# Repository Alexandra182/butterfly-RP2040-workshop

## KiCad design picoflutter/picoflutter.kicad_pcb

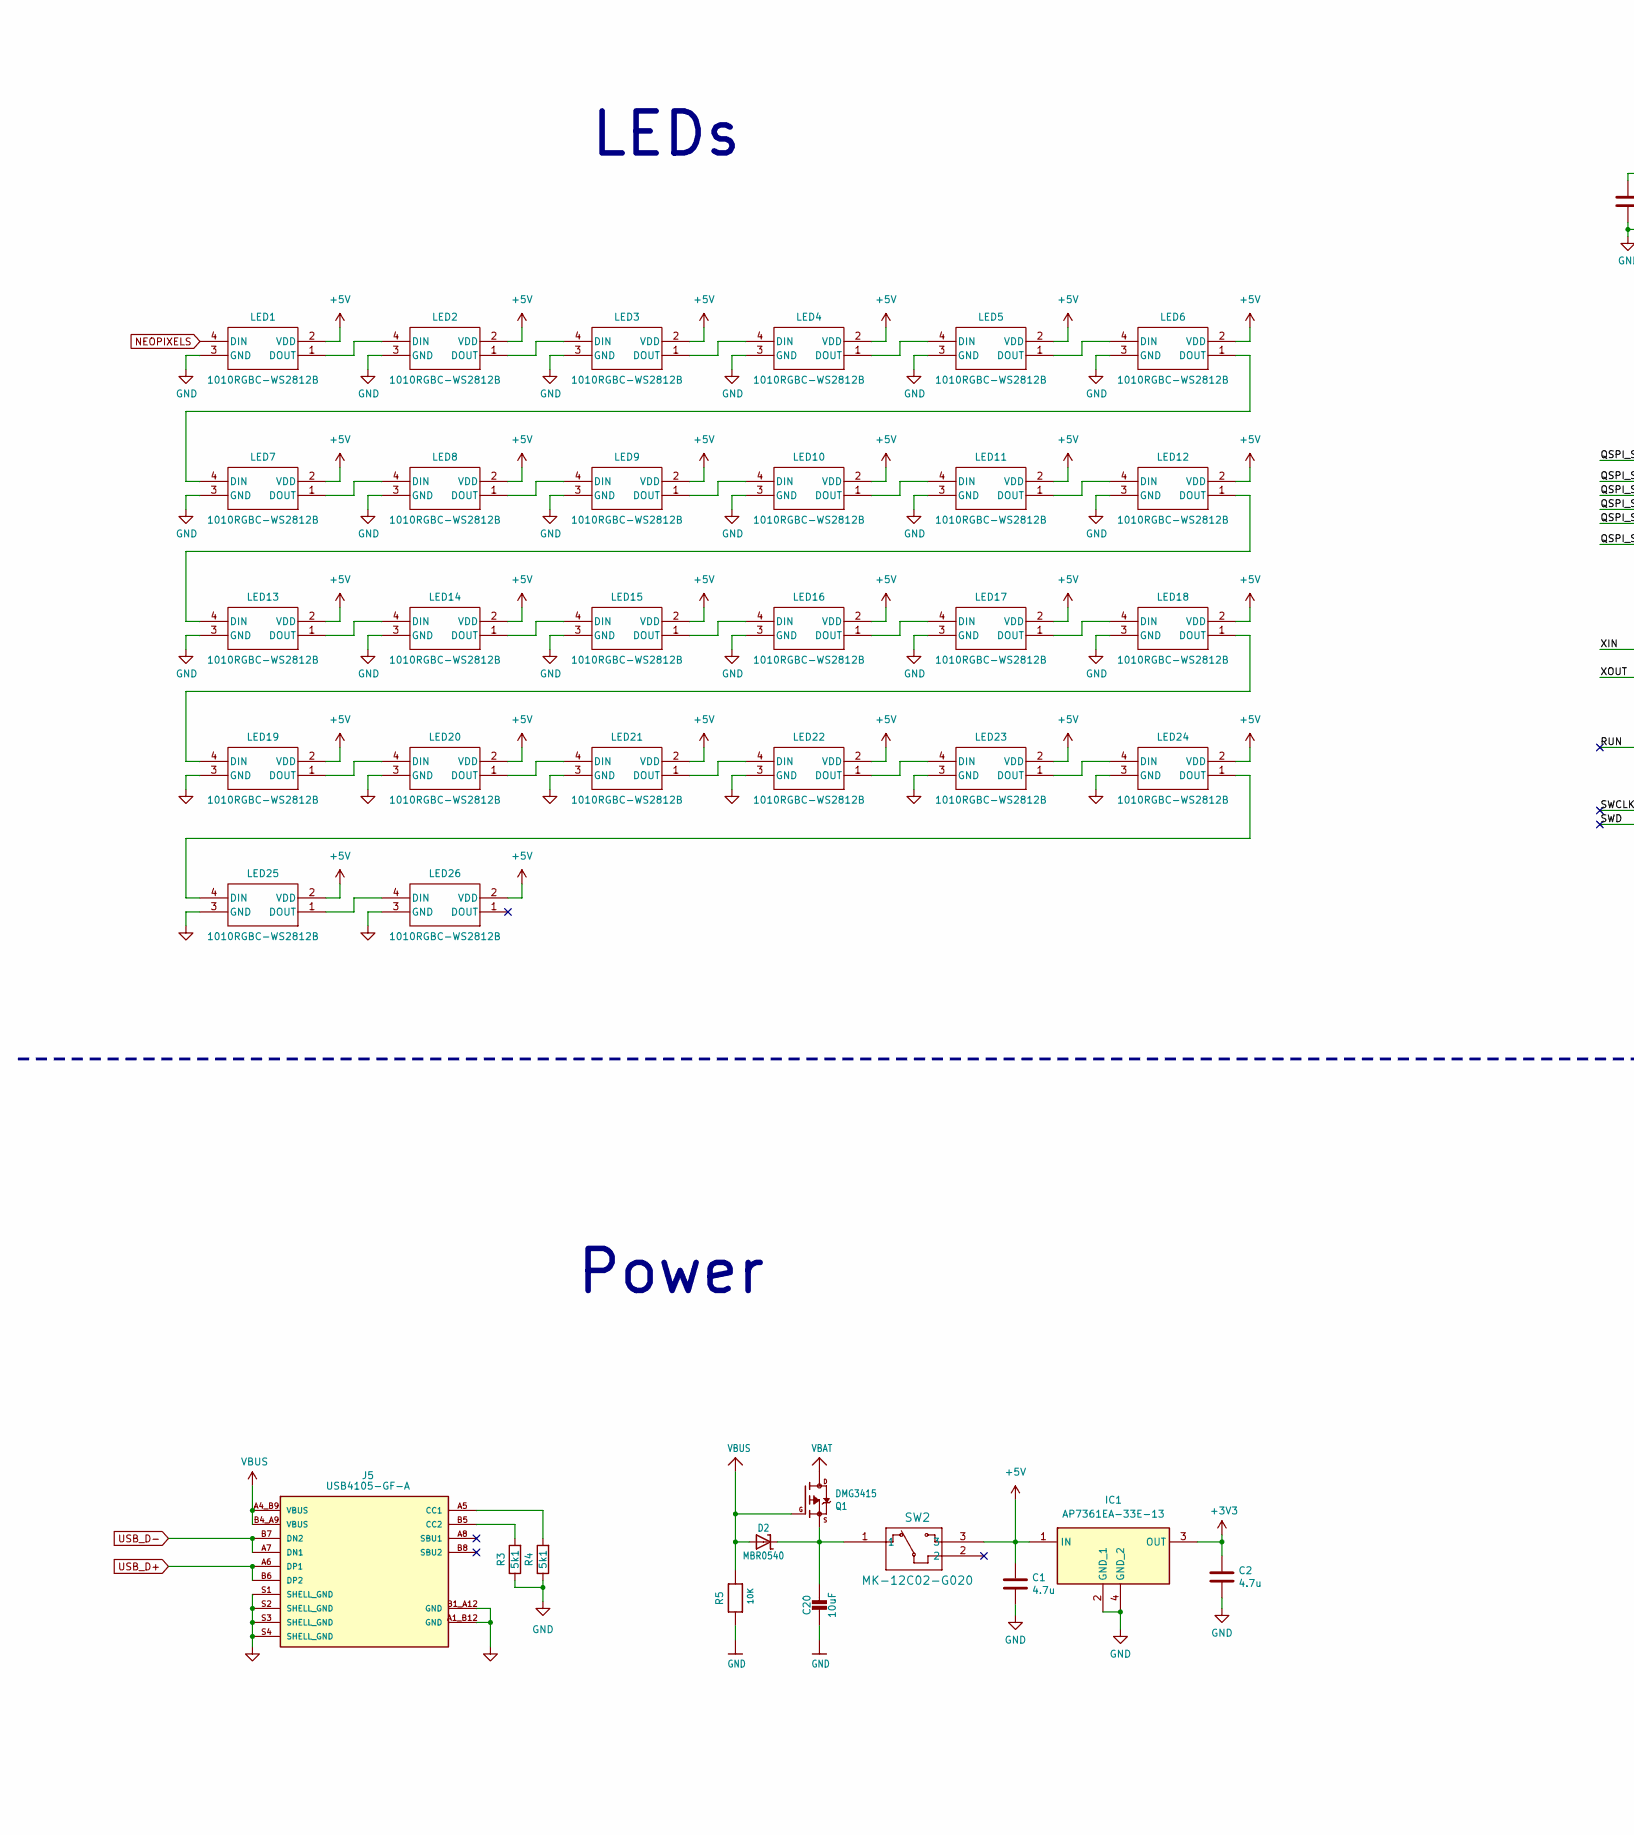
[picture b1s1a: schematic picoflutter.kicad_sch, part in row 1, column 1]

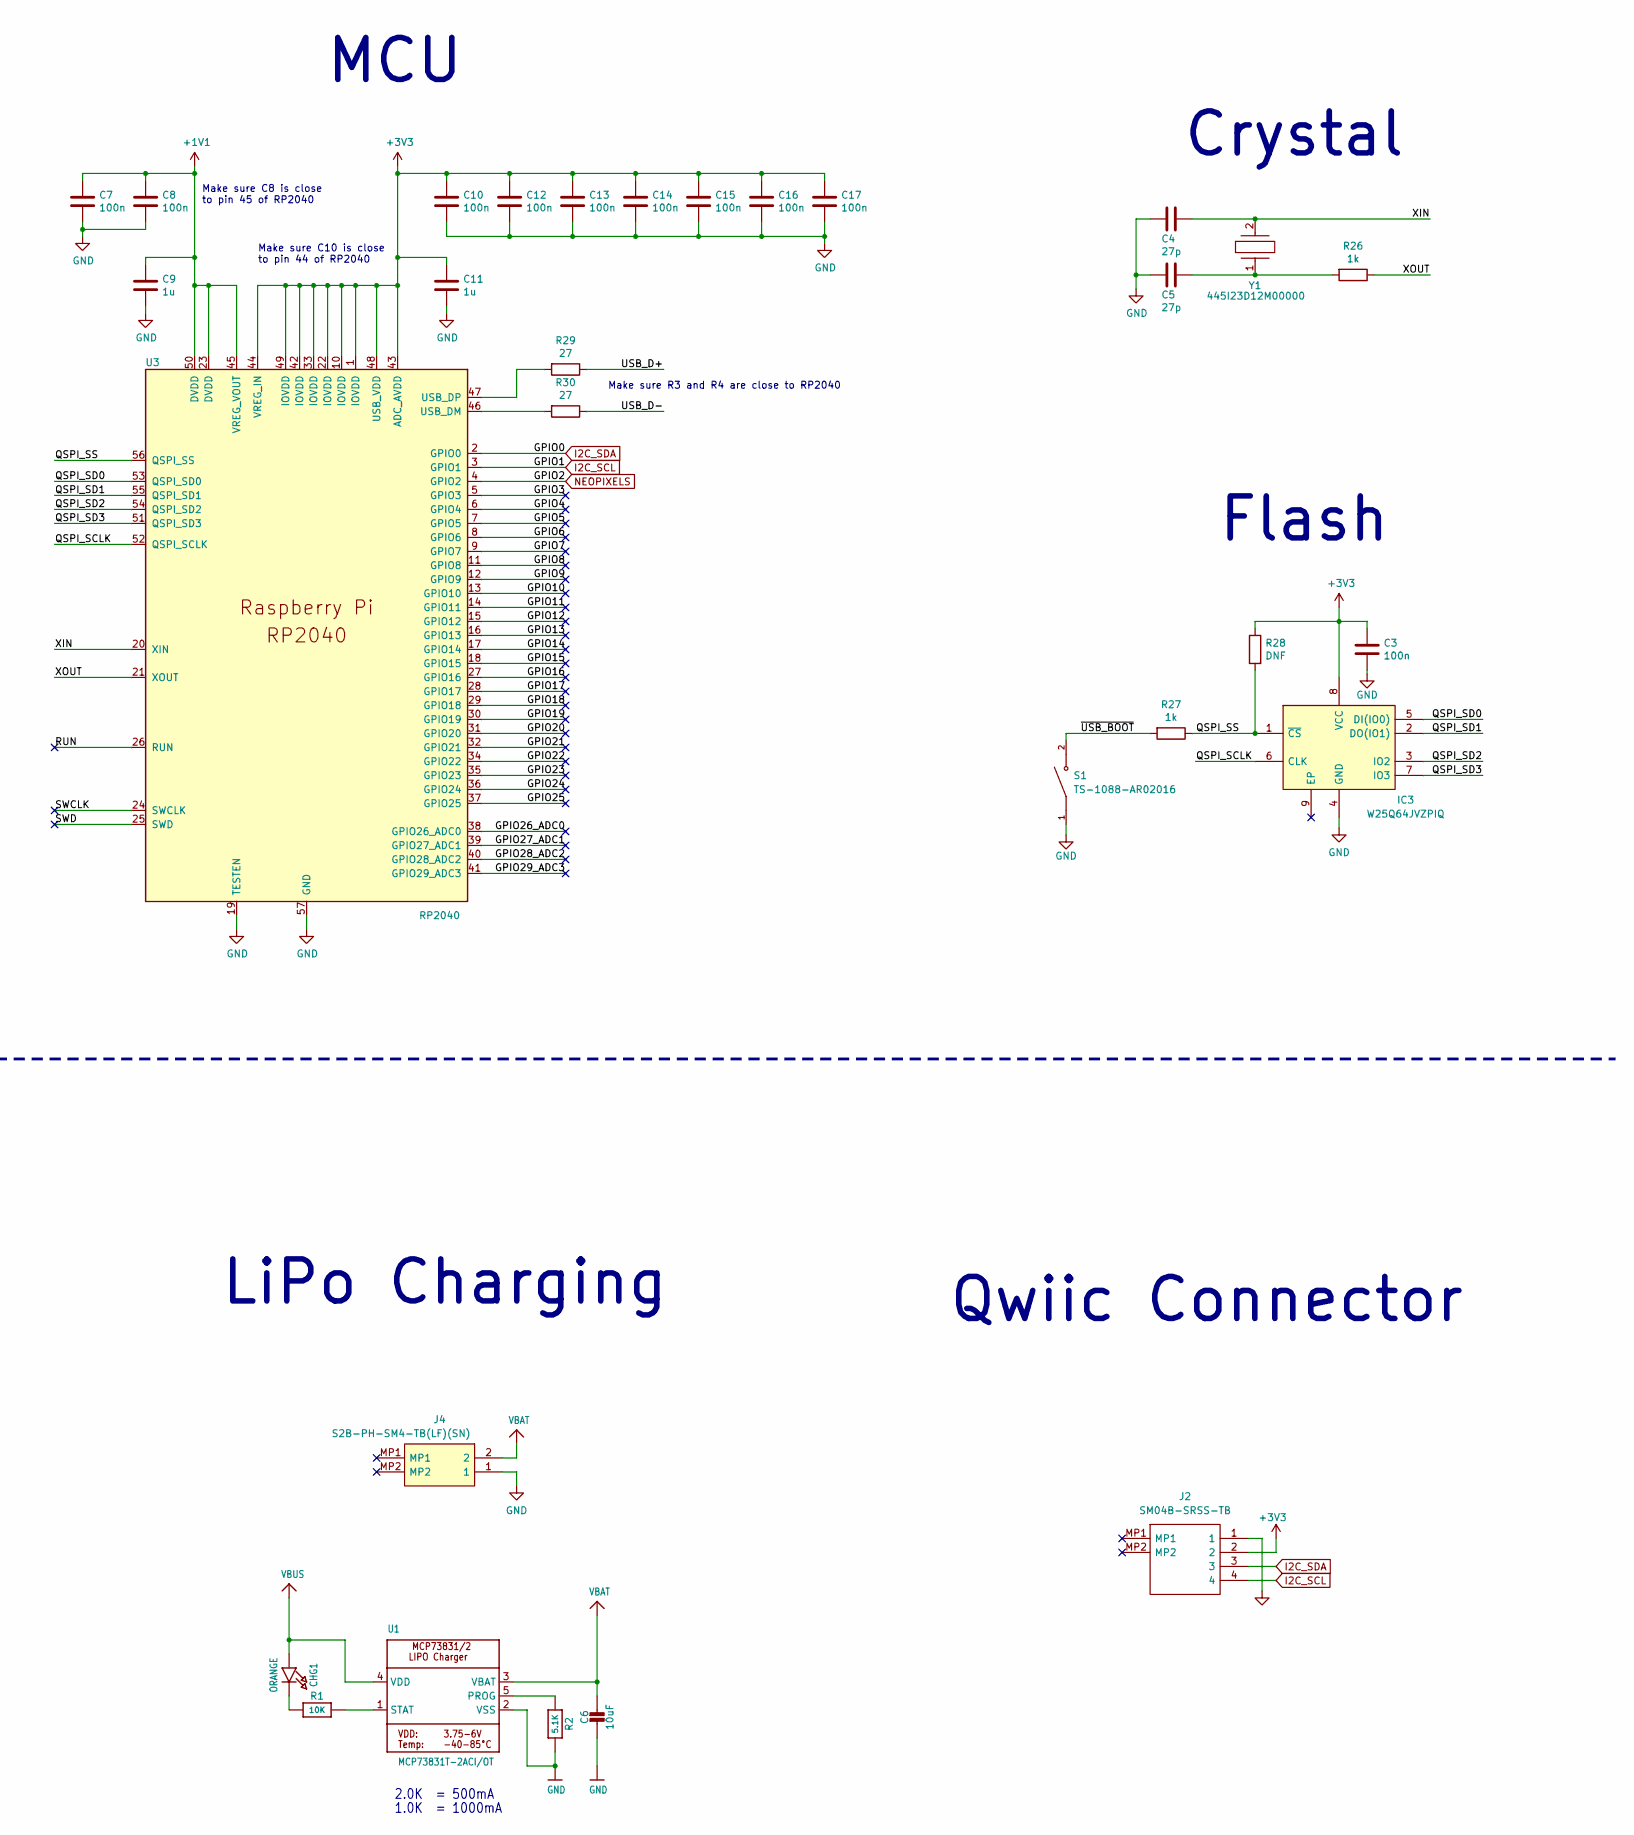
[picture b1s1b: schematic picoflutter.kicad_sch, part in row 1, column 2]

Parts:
C1, C2: 4.7u; C_0603_1608Metric
C3, C7, C8, C10, C12, C13, C14, C15, C16, C17: 100n; C_0402_1005Metric
C4, C5: 27p; C_0402_1005Metric
C6, C20: 10uF; C_0805_2012Metric
C9, C11: 1u; C_0402_1005Metric
CHG1: ORANGE; LED_0402_1005Metric
D2: MBR0540; D_SOD-123
IC1: AP7361EA-33E-13; SOT230P700X180-4N; Mouser Part Number 621-AP7361EA-33E-13
IC3: W25Q64JVZPIQ; SON80P400X400X50-9N; Mouser Part Number 454-W25Q128JVPIM
J2: SM04B-SRSS-TB; SM04BSRSSTB; Manufacturer_Part_Number SM04B-SRSS-TB
J4: S2B-PH-SM4-TB(LF)(SN); JST_PH_S2B-PH-SM4-TB_1x02-1MP_P2.00mm_Horizontal; Mouser Part Number 538-53261-0271
J5: USB4105-GF-A; GCT_USB4105-GF-A; PARTREV A3
LED1, LED2, LED3, LED4, LED5, LED6, LED7, LED8, LED9, LED10, LED11, LED12, LED13, LED14, LED15, LED16, LED17, LED18, LED19, LED20, LED21, LED22, LED23, LED24, LED25, LED26: 1010RGBC-WS2812B; SMD4_XL-1010RGBC_XLG
Q1: DMG3415; SOT-23
R1, R5: 10K; R_0402_1005Metric
R2: 5.1K; R_0402_1005Metric
R3, R4: 5k1; R_0201_0603Metric; Part No AF0201FR-075K1L
R26, R27: 1k; R_0402_1005Metric
R28: DNF; R_0402_1005Metric
R29, R30: 27; R_0402_1005Metric
S1: TS-1088-AR02016; SW_TS-1088-AR02016; PARTREV N/A
SW2: MK-12C02-G020; MK-12C02-G020_GSW
U1: MCP73831T-2ACI/OT; SOT95P270X145-5N
U3: RP2040; RP2040-QFN-56
Y1: 445I23D12M00000; 445I23D24M00000; Mouser Part Number 774-445I23D12M00000

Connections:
I2C_SCL: J2.4, U3.3 (GPIO1)
I2C_SDA: J2.3, U3.2 (GPIO0)
+1V1: C7.1, C8.1, C9.1, U3.23 (DVDD), U3.45 (VREG_VOUT), U3.50 (DVDD)
+3V3: C2.1, C3.1, C10.1, C11.1, C12.1, C13.1, C14.1, C15.1, C16.1, C17.1, IC1.3 (OUT), IC3.8 (VCC), J2.2, R28.1, U3.1 (IOVDD), U3.10 (IOVDD), U3.22 (IOVDD), U3.33 (IOVDD), U3.42 (IOVDD), U3.43 (ADC_AVDD), U3.44 (VREG_IN), U3.48 (USB_VDD), U3.49 (IOVDD)
+5V: C1.1, IC1.1 (IN), LED1.2 (VDD), LED2.2 (VDD), LED3.2 (VDD), LED4.2 (VDD), LED5.2 (VDD), LED6.2 (VDD), LED7.2 (VDD), LED8.2 (VDD), LED9.2 (VDD), LED10.2 (VDD), LED11.2 (VDD), LED12.2 (VDD), LED13.2 (VDD), LED14.2 (VDD), LED15.2 (VDD), LED16.2 (VDD), LED17.2 (VDD), LED18.2 (VDD), LED19.2 (VDD), LED20.2 (VDD), LED21.2 (VDD), LED22.2 (VDD), LED23.2 (VDD), LED24.2 (VDD), LED25.2 (VDD), LED26.2 (VDD), SW2.3
/GPIO3: U3.5 (GPIO3)
/GPIO4: U3.6 (GPIO4)
/GPIO5: U3.7 (GPIO5)
/GPIO6: U3.8 (GPIO6)
/GPIO7: U3.9 (GPIO7)
/GPIO8: U3.11 (GPIO8)
/GPIO9: U3.12 (GPIO9)
/GPIO10: U3.13 (GPIO10)
/GPIO11: U3.14 (GPIO11)
/GPIO12: U3.15 (GPIO12)
/GPIO13: U3.16 (GPIO13)
/GPIO14: U3.17 (GPIO14)
/GPIO15: U3.18 (GPIO15)
/GPIO16: U3.27 (GPIO16)
/GPIO17: U3.28 (GPIO17)
/GPIO18: U3.29 (GPIO18)
/GPIO19: U3.30 (GPIO19)
/GPIO20: U3.31 (GPIO20)
/GPIO21: U3.32 (GPIO21)
/GPIO22: U3.34 (GPIO22)
/GPIO23: U3.35 (GPIO23)
/GPIO24: U3.36 (GPIO24)
/GPIO25: U3.37 (GPIO25)
/GPIO26_ADC0: U3.38 (GPIO26_ADC0)
/GPIO27_ADC1: U3.39 (GPIO27_ADC1)
/GPIO28_ADC2: U3.40 (GPIO28_ADC2)
/GPIO29_ADC3: U3.41 (GPIO29_ADC3)
/QSPI_SCLK: IC3.6 (CLK), U3.52 (QSPI_SCLK)
/QSPI_SD0: IC3.5 (DI(IO0)), U3.53 (QSPI_SD0)
/QSPI_SD1: IC3.2 (DO(IO1)), U3.55 (QSPI_SD1)
/QSPI_SD2: IC3.3 (IO2), U3.54 (QSPI_SD2)
/QSPI_SD3: IC3.7 (IO3), U3.51 (QSPI_SD3)
/QSPI_SS: IC3.1 (~CS), R27.1, R28.2, U3.56 (QSPI_SS)
/RUN: U3.26 (RUN)
/SWCLK: U3.24 (SWCLK)
/SWD: U3.25 (SWD)
/XIN: C4.1, U3.20 (XIN), Y1.2
/XOUT: R26.1, U3.21 (XOUT)
/~USB_BOOT: R27.2, S1.2
GND: C1.2, C2.2, C3.2, C4.2, C5.2, C6.2, C7.2, C8.2, C9.2, C10.2, C11.2, C12.2, C13.2, C14.2, C15.2, C16.2, C17.2, C20.2, IC1.2 (GND_1), IC1.4 (GND_2), IC3.4 (GND), J2.1, J4.1, J5.A1_B12 (GND), J5.B1_A12 (GND), J5.S1 (SHELL_GND), J5.S2 (SHELL_GND), J5.S3 (SHELL_GND), J5.S4 (SHELL_GND), LED1.3 (GND), LED2.3 (GND), LED3.3 (GND), LED4.3 (GND), LED5.3 (GND), LED6.3 (GND), LED7.3 (GND), LED8.3 (GND), LED9.3 (GND), LED10.3 (GND), LED11.3 (GND), LED12.3 (GND), LED13.3 (GND), LED14.3 (GND), LED15.3 (GND), LED16.3 (GND), LED17.3 (GND), LED18.3 (GND), LED19.3 (GND), LED20.3 (GND), LED21.3 (GND), LED22.3 (GND), LED23.3 (GND), LED24.3 (GND), LED25.3 (GND), LED26.3 (GND), R2.2, R3.1, R4.1, R5.1, S1.1, U1.2 (VSS), U3.19 (TESTEN), U3.57 (GND)
NEOPIXELS: LED1.4 (DIN), U3.4 (GPIO2)
unnamed: C5.1, R26.2, Y1.1
unnamed: CHG1.1 (C), R1.1
unnamed: C20.1, D2.1 (C), Q1.2 (S), SW2.1
unnamed: J5.A5 (CC1), R4.2
unnamed: J5.B5 (CC2), R3.2
unnamed: LED1.1 (DOUT), LED2.4 (DIN)
unnamed: LED2.1 (DOUT), LED3.4 (DIN)
unnamed: LED3.1 (DOUT), LED4.4 (DIN)
unnamed: LED4.1 (DOUT), LED5.4 (DIN)
unnamed: LED5.1 (DOUT), LED6.4 (DIN)
unnamed: LED6.1 (DOUT), LED7.4 (DIN)
unnamed: LED7.1 (DOUT), LED8.4 (DIN)
unnamed: LED8.1 (DOUT), LED9.4 (DIN)
unnamed: LED9.1 (DOUT), LED10.4 (DIN)
unnamed: LED10.1 (DOUT), LED11.4 (DIN)
unnamed: LED11.1 (DOUT), LED12.4 (DIN)
unnamed: LED12.1 (DOUT), LED13.4 (DIN)
unnamed: LED13.1 (DOUT), LED14.4 (DIN)
unnamed: LED14.1 (DOUT), LED15.4 (DIN)
unnamed: LED15.1 (DOUT), LED16.4 (DIN)
unnamed: LED16.1 (DOUT), LED17.4 (DIN)
unnamed: LED17.1 (DOUT), LED18.4 (DIN)
unnamed: LED18.1 (DOUT), LED19.4 (DIN)
unnamed: LED19.1 (DOUT), LED20.4 (DIN)
unnamed: LED20.1 (DOUT), LED21.4 (DIN)
unnamed: LED21.1 (DOUT), LED22.4 (DIN)
unnamed: LED22.1 (DOUT), LED23.4 (DIN)
unnamed: LED23.1 (DOUT), LED24.4 (DIN)
unnamed: LED24.1 (DOUT), LED25.4 (DIN)
unnamed: LED25.1 (DOUT), LED26.4 (DIN)
unnamed: R2.1, U1.5 (PROG)
unnamed: R1.2, U1.1 (STAT)
unnamed: R30.2, U3.46 (USB_DM)
unnamed: R29.2, U3.47 (USB_DP)
USB_D+: J5.A6 (DP1), J5.B6 (DP2), R29.1
USB_D-: J5.A7 (DN1), J5.B7 (DN2), R30.1
VBAT: C6.1, J4.2, Q1.3 (D), U1.3 (VBAT)
VBUS: CHG1.2 (A), D2.2 (A), J5.A4_B9 (VBUS), J5.B4_A9 (VBUS), Q1.1 (G), R5.2, U1.4 (VDD)

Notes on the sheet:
2.0K = 500mA
Crystal
Make sure C10 is close to pin 44 of RP2040
Power
LEDs
LiPo Charging
1.0K = 1000mA
Make sure C8 is close to pin 45 of RP2040
Qwiic Connector
Make sure R3 and R4 are close to RP2040
Flash
MCU

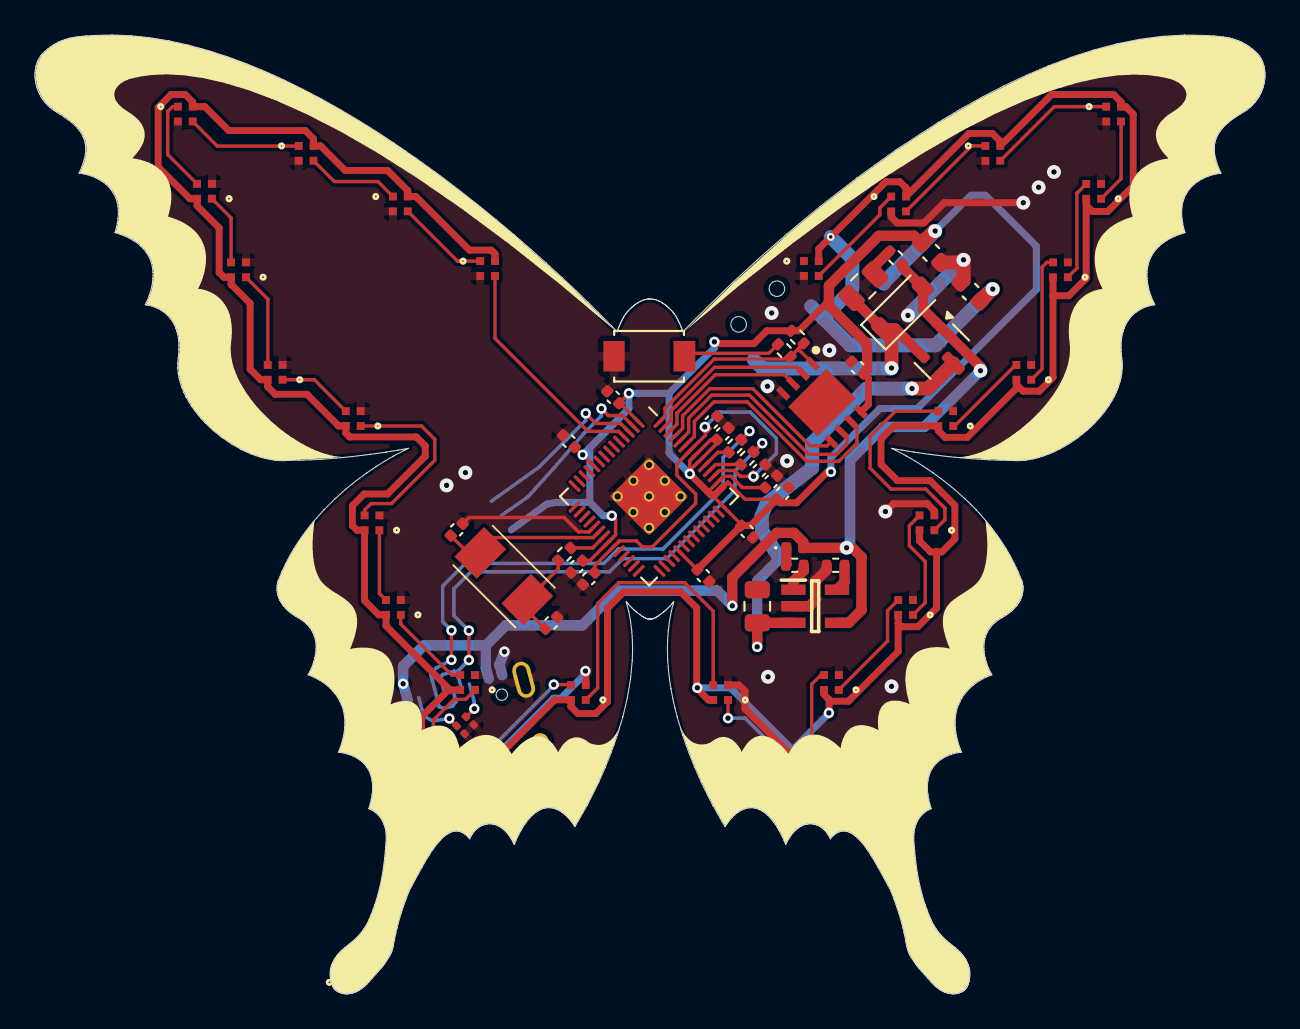
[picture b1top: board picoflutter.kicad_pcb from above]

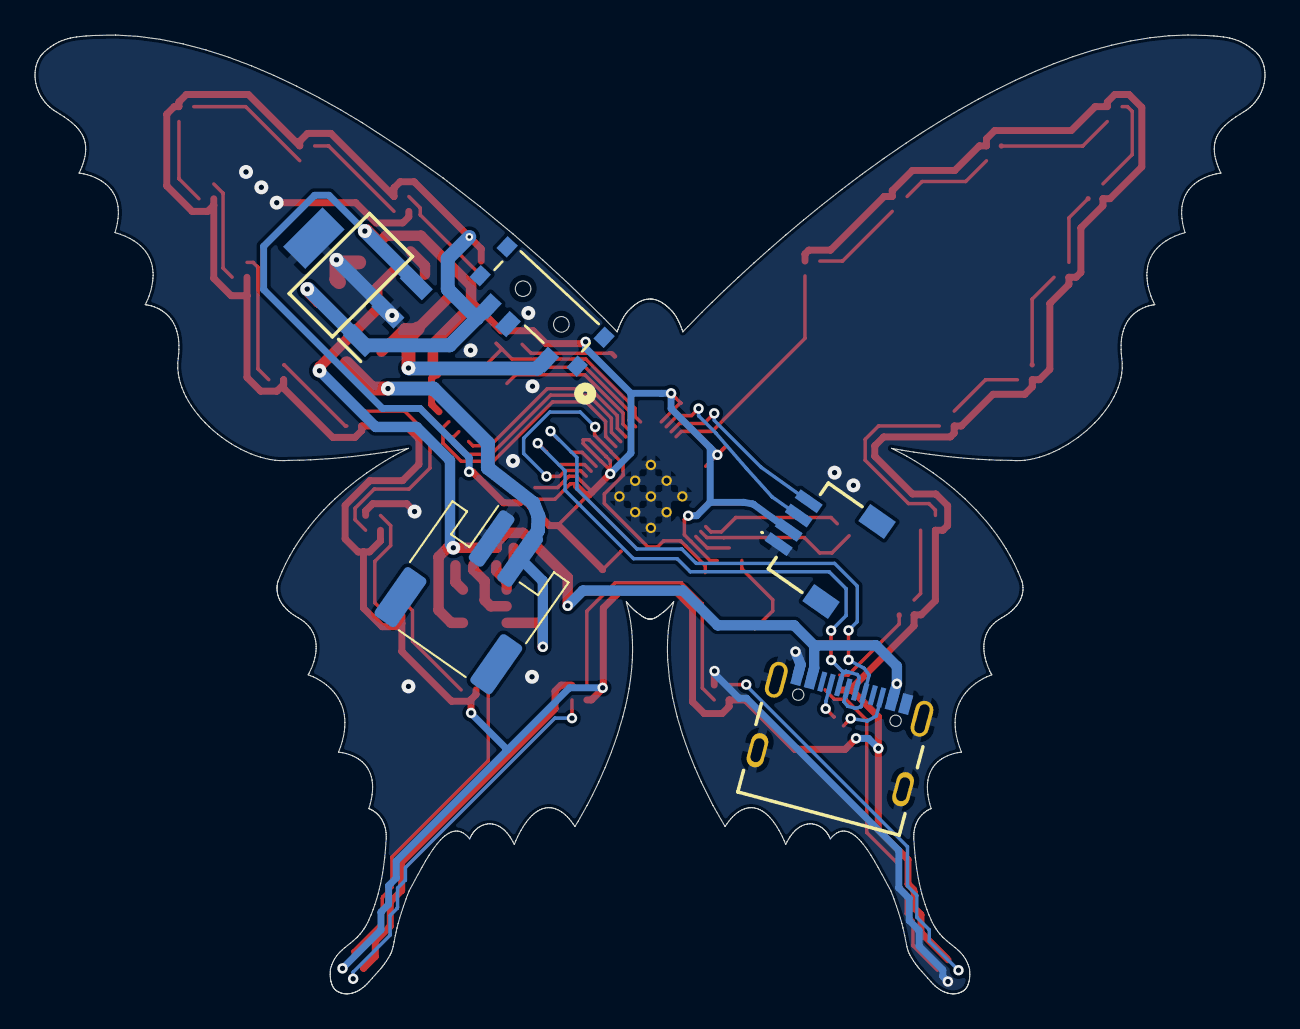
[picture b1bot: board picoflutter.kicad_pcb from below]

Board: 4 copper layers, 70.5 x 55.0 mm, 67 parts (5 on the bottom side), 54 nets.

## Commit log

2025-08-12 initial PCB
2025-09-04 fixed leds power supply
2025-09-04 EasyEDA multi-color silkscreen Gerbers
2025-09-04 EasyEDA multi-color silkscreen gerbers - Quetzal
